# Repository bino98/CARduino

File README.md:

## License
* MIT  
    * see LICENSE

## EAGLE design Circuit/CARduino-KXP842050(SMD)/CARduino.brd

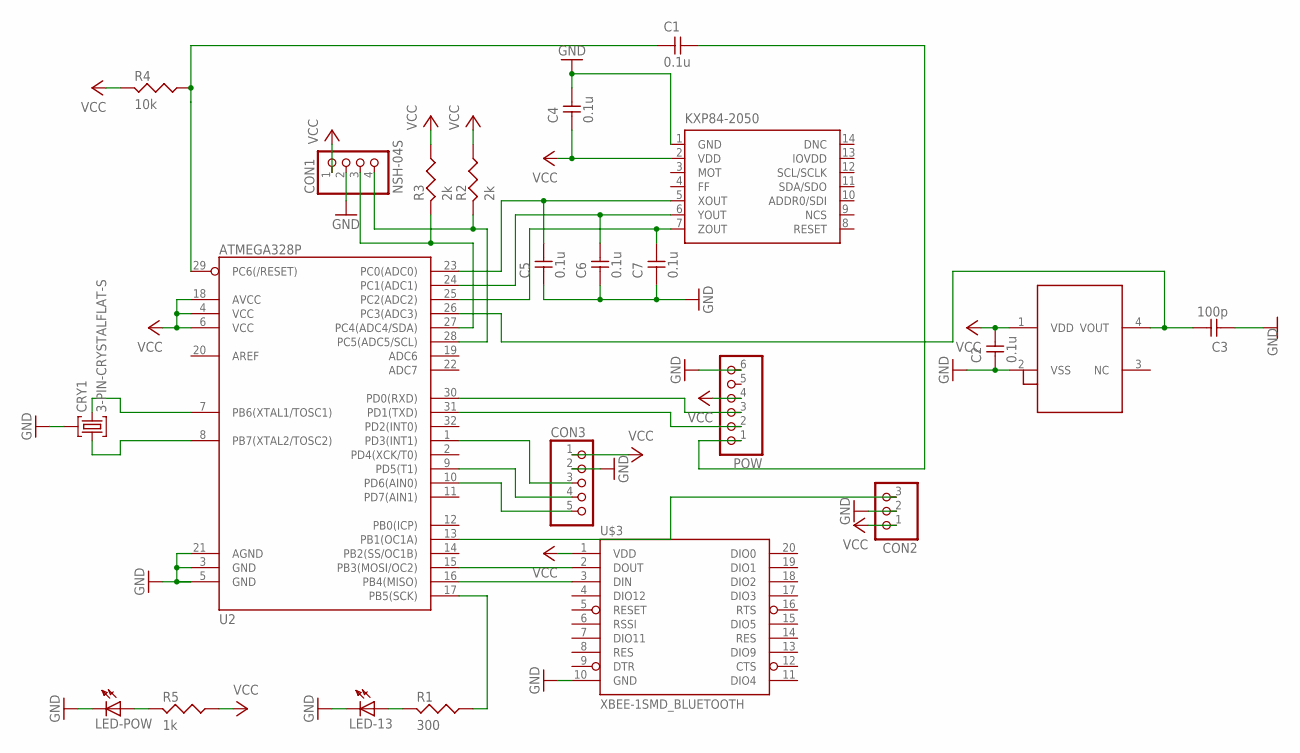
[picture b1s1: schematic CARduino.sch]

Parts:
C1, C2, C4, C5, C6, C7: 0.1u; 1608
C3: 100p; 1608
CON1: NSH-04S; NSH-04-S
CON2: NSH-03S; NSH-03-S
CON3: PINHD-1X5DIP; 1X05
CRY1: 3-PIN-CRYSTALFLAT-S; CRYSTAL-CSTCE8M
LED-13: 1608
LED-POW: 1608
POW: PINHD-1X6NORMAL; 1X06
R1: 300; 1608
R2, R3: 2k; 1608
R4: 10k; 1608
R5: 1k; 1608
S1: TEMPERATURE-S8120C; SC-82AB
U2: ATMEGA328P; TQFP32-08
U$1: KXP84-2050; DFN14-5X5
U$3: XBEE-1SMD_BLUETOOTH; XBEE-SMD_BLUETOOTH

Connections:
GND: C2.P$1 (1), C3.P$1 (1), C4.P$2 (2), C5.P$1 (1), C6.P$1 (1), C7.P$1 (1), CON1.2, CON2.2, CON3.2, CRY1.G (GND), LED-13.C, LED-POW.C, POW.6, S1.2 (VSS), U2.3 (GND), U2.5 (GND), U2.21 (AGND), U$1.1 (GND), U$3.10 (GND)
IOVDD: U$1.13 (IOVDD)
unnamed: CRY1.O1 (1), U2.8 (PB7(XTAL2/TOSC2))
unnamed: CRY1.O2 (2), U2.7 (PB6(XTAL1/TOSC1))
unnamed: C3.P$2 (2), S1.4 (VOUT), U2.26 (PC3(ADC3))
unnamed: C5.P$2 (2), U2.23 (PC0(ADC0)), U$1.5 (XOUT)
unnamed: C6.P$2 (2), U2.24 (PC1(ADC1)), U$1.6 (YOUT)
unnamed: U2.15 (PB3(MOSI/OC2)), U$3.2 (DOUT)
unnamed: U2.16 (PB4(MISO)), U$3.3 (DIN)
unnamed: C7.P$2 (2), U2.25 (PC2(ADC2)), U$1.7 (ZOUT)
unnamed: R1.1, U2.17 (PB5(SCK))
unnamed: LED-POW.A, R5.2
unnamed: LED-13.A, R1.2
unnamed: CON3.3, U2.1 (PD3(INT1))
unnamed: CON3.4, U2.9 (PD5(T1))
unnamed: CON2.3, U2.13 (PB1(OC1A))
unnamed: CON1.3, R3.2, U2.27 (PC4(ADC4/SDA))
unnamed: CON1.4, R2.2, U2.28 (PC5(ADC5/SCL))
unnamed: C1.P$2 (2), POW.1
unnamed: C1.P$1 (1), R4.1, U2.29 (PC6(/RESET))
unnamed: POW.3, U2.30 (PD0(RXD))
unnamed: POW.2, U2.31 (PD1(TXD))
unnamed: CON3.5, U2.10 (PD6(AIN0))
VCC: C2.P$2 (2), C4.P$1 (1), CON1.1, CON2.1, CON3.1, POW.4, R2.1, R3.1, R4.2, R5.1, S1.1 (VDD), U2.4 (VCC), U2.6 (VCC), U2.18 (AVCC), U$1.2 (VDD), U$3.1 (VDD)

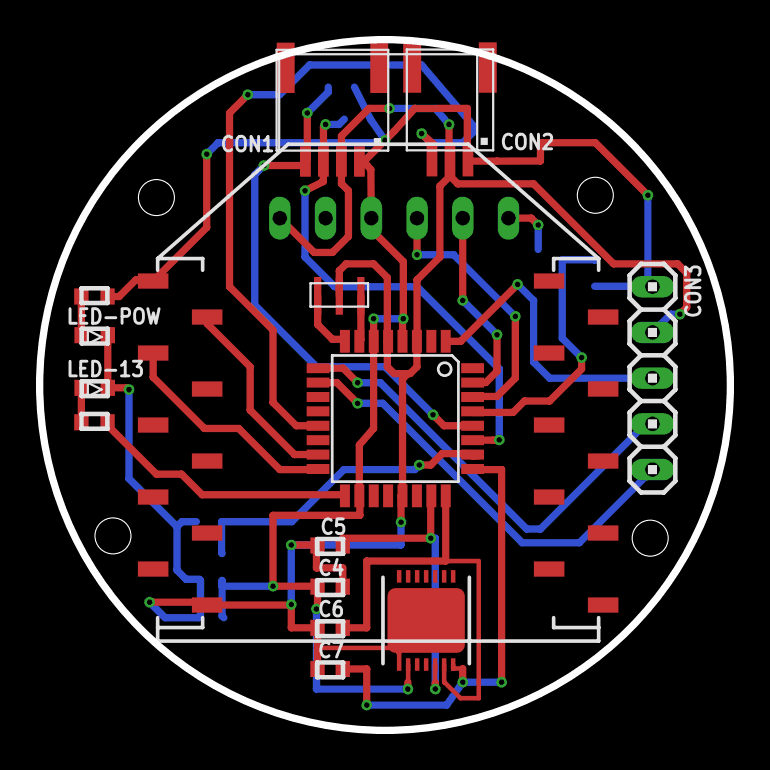
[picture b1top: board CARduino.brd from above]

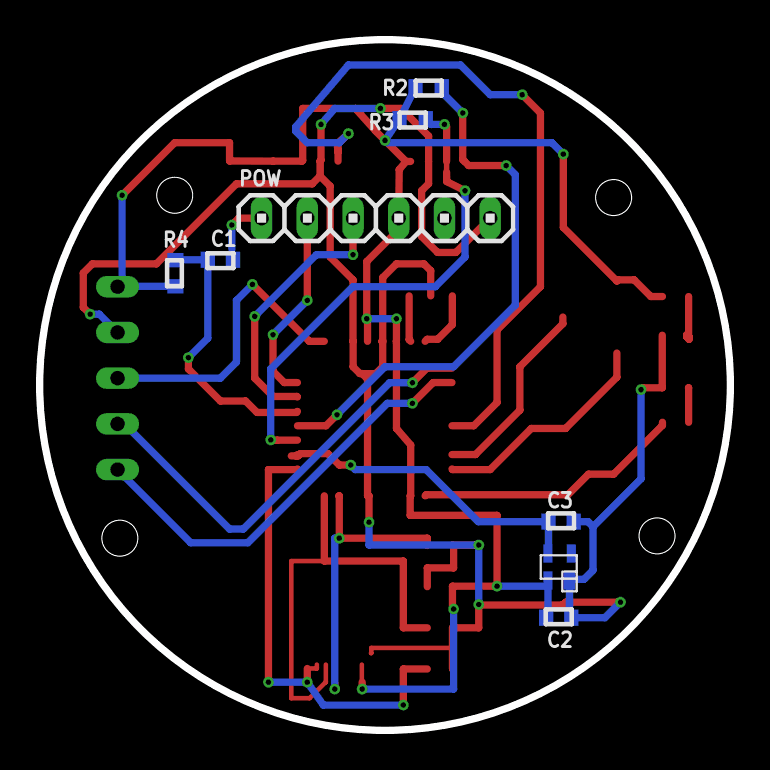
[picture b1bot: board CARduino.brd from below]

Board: 2 copper layers, 38.4 x 38.4 mm, 23 parts (8 on the bottom side), 23 nets.

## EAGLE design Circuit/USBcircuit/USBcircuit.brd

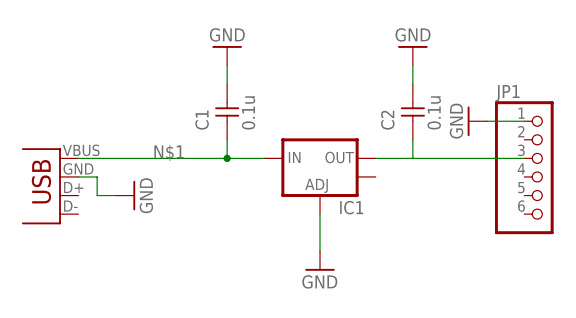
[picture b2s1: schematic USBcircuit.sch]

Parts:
C1, C2: 0.1u; 1608
IC1: V_REG_LM1117SOT223; SOT223
JP1: PINHD-1X6NORMAL; 1X06
JP3: USB-A-H

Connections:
GND: C1.P$2 (2), C2.P$2 (2), IC1.1 (ADJ), JP1.1, JP3.GND (VBUS)
unnamed: C1.P$1 (1), IC1.3 (IN), JP3.VBUS (GND)
unnamed: C2.P$1 (1), IC1.2 (OUT), JP1.3

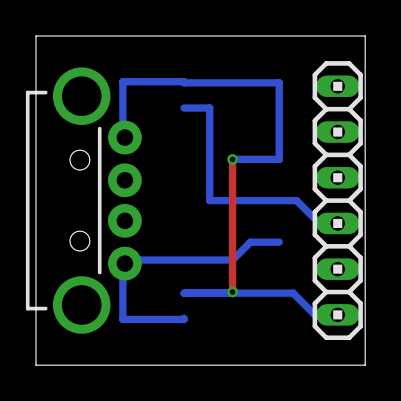
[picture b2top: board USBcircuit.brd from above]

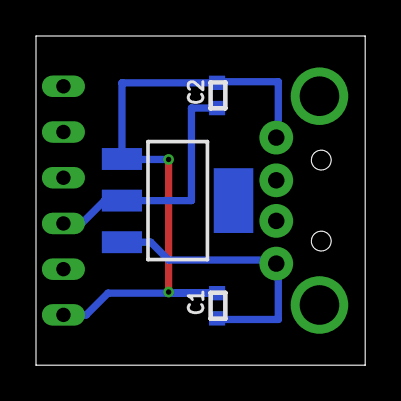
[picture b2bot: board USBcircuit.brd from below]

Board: 2 copper layers, 18.3 x 18.3 mm, 5 parts (3 on the bottom side), 3 nets.

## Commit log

2015-03-01 remove P板データ
2015-03-01 write License & Readme

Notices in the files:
parts and their libraries:
SparkFun-DigitalIC: Licensing: CC v3.0 Share-Alike You are welcome to use this library for commercial purposes.
